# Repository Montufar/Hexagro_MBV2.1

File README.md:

# Hexagro_MBV2.1
Schematic, BOM and PCB layout of V2.1 Motherboard

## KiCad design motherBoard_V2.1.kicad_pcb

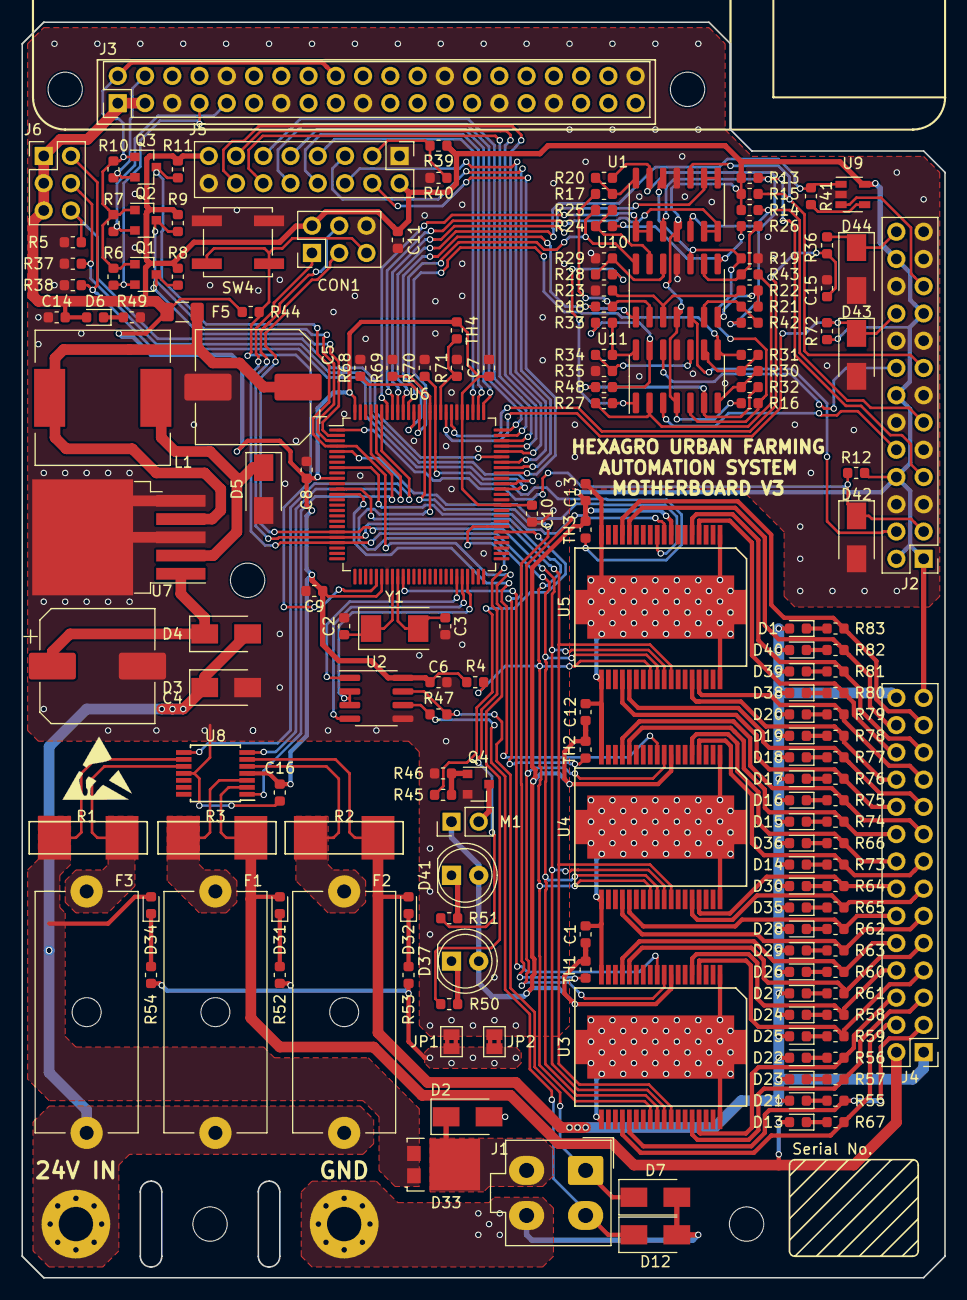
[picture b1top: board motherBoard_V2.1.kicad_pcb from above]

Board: 2 copper layers, 86.0 x 117.0 mm, 175 parts (0 on the bottom side), 155 nets.

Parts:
C1, C12, C13: 1uF; C_0603_1608Metric
C2, C3: 18pF; C_0603_1608Metric
C4: 680uF; CP_Elec_10x10.5
C5: 220uF; CP_Elec_10x10.5
C6, C7, C8, C9, C10, C11, C14, C15: 100nF; C_0603_1608Metric
C16: 100 nF; C_0603_1608Metric
CON1: AVR-ISP-6; PinHeader_2x03_P2.54mm_Vertical
D1, D6, D13, D14, D15, D16, D17, D18, D19, D20, D21, D22, D23, D24, D25, D26, D27, D28, D29, D30, D31, D32, D34, D35, D36, D38, D39, D40: LED; LED_0603_1608Metric
D2: D_TVS_24V; D_SMA
D3, D4, D5: D; D_SMA
D7, D12, D42, D43, D44: D_TVS_5V; D_SMA
D33: STPS1045SF; TO-277A
D37, D41: LED_ALT; LED_D5.0mm
F1, F2: 1 A; Fuseholder_Cylinder-5x20mm_Schurter_0031_8201_Horizontal_Op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
F3: 7.5 A; Fuseholder_Cylinder-5x20mm_Schurter_0031_8201_Horizontal_Op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
F5: 1A; Fuse_1206_3216Metric
J1: Conn_LEDs; Molex_Mini-Fit_Jr_5566-04A_2x02_P4.20mm_Vertical
J2: Conn_02x13_Odd_Even; PinHeader_2x13_P2.54mm_Vertical
J3: Conn_RPi3; PinHeader_2x20_P2.54mm_Vertical
J4: Conn_02x14_Odd_Even; PinHeader_2x14_P2.54mm_Vertical
J5: Conn_02x08_Odd_Even; PinHeader_2x08_P2.54mm_Vertical
J6: Conn_02x03_Odd_Even; PinHeader_2x03_P2.54mm_Vertical
JP1, JP2: SolderJumper_2_Bridged; SolderJumper-2_P1.3mm_Bridged2Bar_Pad1.0x1.5mm
L1: 33uH; L_12x12mm_H8mm
M1: Fan; PinHeader_1x02_P2.54mm_Vertical
Q1, Q2, Q3: BSS138; SOT-23
Q4: 2N7002; SOT-23
R1: 10m; OARS1
R2, R3: 50m; OARS1
R4, R5, R6, R7, R8, R9, R10, R11, R12, R13, R14, R15, R37, R38, R40, R41, R44, R46, R68, R69, R70, R71: 10k; R_0603_1608Metric
R16, R19, R49, R50, R51: 1k; R_0603_1608Metric
R17, R18, R22, R23, R24, R25, R28, R29, R30, R31, R34, R35: 40k; R_0603_1608Metric
R20, R21, R26, R27, R32, R33: 25k; R_0603_1608Metric
R36, R42, R43, R45, R47, R48: 100; R_0603_1608Metric
R39: 27k; R_0603_1608Metric
R52, R53, R54, R55, R56, R57, R58, R59, R60, R61, R62, R63, R64, R65, R66, R67, R72, R73, R74, R75, R76, R77, R78, R79, R80, R81, R82, R83: 22k; R_0603_1608Metric
SW4: SW_Push; SW_Push_1P1T_NO_CK_KSC6xxJ
TH1, TH2, TH3, TH4: Thermistor_NTC; R_0603_1608Metric
U1, U10, U11: MCP6004; SOIC-14_3.9x8.7mm_P1.27mm
U2: MAX485E; SOIC-8_3.9x4.9mm_P1.27mm
U3, U4, U5: TLE6230GP; PG-DSO-36
U6: ATMEGA2560-16AU; TQFP-100_14x14mm_P0.5mm
U7: LM2596S-5; TO-263-5_TabPin3
U8: INA4180A2IPWR; TSSOP-14_4.4x5mm_P0.65mm
U9: MCP6001; SOT-23-5
Y1: 16 MHz; Crystal_SMD_0603-2Pin_6.0x3.5mm

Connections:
+5V: C1.1, C6.1, C7.1, C8.1, C9.1, C10.1, C11.1, C12.1, C13.1, C14.1, C16.1, CON1.2, D6.2, D37.2, D41.2, F5.1, J2.1, J2.2, J2.8, J2.14, J2.19, J2.24, J3.1, J3.3, J4.27, J5.2, J5.15, J6.1, J6.3, J6.5, M1.1, R4.1, R8.1, R9.1, R11.1, R12.2, R13.1, R14.1, R15.1, R16.1, R39.1, R44.1, R72.1, TH1.1, TH2.1, TH3.1, TH4.1, U1.4, U2.8, U3.8, U4.8, U5.8, U6.10, U6.31, U6.61, U6.80, U6.100, U8.4, U9.5, U10.4, U11.4
+24V_IN: D3.1, D4.2, F1.2, F2.2, F3.2
+24V_LEDS: D33.1, D33.2, D34.2, R1.1, U8.9
+24V_PUMP: D13.2, D31.2, J4.2, R3.1, U8.2
+24V_VALVES: D1.2, D14.2, D15.2, D16.2, D17.2, D18.2, D19.2, D20.2, D21.2, D22.2, D23.2, D24.2, D25.2, D26.2, D27.2, D28.2, D29.2, D30.2, D32.2, D35.2, D36.2, D38.2, D39.2, D40.2, J4.1, J4.28, R2.1, U8.6
/CO2_SIG: D44.1, J2.26, R36.2
/DHT_SIG: D42.1, J2.3, R12.1, U6.1
/IN+1: F1.1, R3.2, U8.3
/IN+2: F2.1, R2.2, U8.5
/IN+3: F3.1, R1.2, U8.10
/LC_1: J2.4, U10.5
/LC_2: J2.10, U11.3
/LC_3: J2.16, U11.12
/LS_SIG: D43.1, J2.20, R72.2, U6.83
/MCU/ADC0: U6.97, U8.1
/MCU/ADC1: U6.96, U8.7
/MCU/ADC2: U6.95, U8.8
/MCU/ADC3: U1.1, U1.2, U6.94
/MCU/ADC4: U1.6, U1.7, U6.93
/MCU/ADC5: U1.8, U1.9, U6.92
/MCU/ADC6: R41.1, U6.91, U9.1
/MCU/ADC7: R18.1, U6.90, U10.1
/MCU/ADC8: R25.1, U6.89, U10.14
/MCU/ADC9: R31.1, U6.88, U11.8
/MCU/ADC10: R68.1, TH1.2, U6.87
/MCU/ADC11: R69.1, TH2.2, U6.86
/MCU/ADC12: R70.1, TH3.2, U6.85
/MCU/ADC13: R71.1, TH4.2, U6.84
/MCU/ADC15: C15.1, R36.1, U6.82
/MCU/DRV_FLT: R4.2, U3.26, U4.26, U5.26, U6.12
/MCU/DRV_RESET: U3.9, U4.9, U5.9, U6.8
/MCU/MCU_RESET: CON1.5, R44.2, SW4.2, U6.30
/MCU/MISO: CON1.1, U3.27, U4.27, U5.27, U6.22
/MCU/MOSI: CON1.4, U3.29, U4.29, U5.29, U6.21
/MCU/RX0_MCU: Q1.3, R8.2, U6.2
/MCU/SCK: CON1.3, U3.28, U4.28, U5.28, U6.20
/MCU/ctrl_mod: J6.6, R5.1, U6.70
/MCU/ctrl_run: J6.2, R38.1, U6.64
/MCU/ctrl_sel: J6.4, R37.1, U6.65
/MCU/disp_db0: J5.7, U6.78
/MCU/disp_db1: J5.8, U6.77
/MCU/disp_db2: J5.9, U6.76
/MCU/disp_db3: J5.10, U6.75
/MCU/disp_db4: J5.11, U6.74
/MCU/disp_db5: J5.12, U6.73
/MCU/disp_db6: J5.13, U6.72
/MCU/disp_db7: J5.14, U6.71
/MCU/disp_e: J5.6, U6.69
/MCU/disp_rs: J5.4, U6.67
/MCU/disp_rw: J5.5, U6.68
/NTC_W1: J2.7, R13.2, U1.3
/NTC_W2: J2.11, R14.2, U1.5
/NTC_W3: J2.15, R15.2, U1.10
/RS485/DE: U2.2, U2.3, U6.47
/RS485/DI: U2.4, U6.46
/RS485/RO: U2.1, U6.45
/RaspberryPi3Conn/3V3_RPI: J3.2, J3.18, Q1.1, Q2.1, Q3.1, R6.1, R7.1, R10.1
/RaspberryPi3Conn/GPIO2_RPI: J3.4, Q3.2, R10.2
/RaspberryPi3Conn/RX_RPI: Q2.3, R9.2, U6.3
/RaspberryPi3Conn/UART0_RX_RPI: J3.9, Q2.2, R7.2
/RaspberryPi3Conn/UART0_TX_RPI: J3.7, Q1.2, R6.2
/WPS_SIG: J2.21, U9.3
/fanDriver/DRIVE: R45.2, U6.56
/lowSideDriver1/CS: U3.10, U6.35
/lowSideDriver2/CS: U4.10, U6.13
/lowSideDriver3/CS: U5.10, U6.5
GND: C2.2, C3.2, C4.2, C5.2, C6.2, C7.2, C8.2, C9.2, C10.2, C11.2, C14.2, C15.2, C16.2, CON1.6, D3.2, D5.2, D42.2, D43.2, D44.2, J2.5, J2.6, J2.9, J2.12, J2.13, J2.17, J2.18, J2.22, J2.23, J2.25, J3.5, J3.10, J3.13, J3.19, J3.26, J3.29, J3.33, J3.40, J5.1, J5.16, JP1.2, JP2.2, Q4.2, R5.2, R19.2, R23.1, R29.1, R35.1, R37.2, R38.2, R40.2, R46.1, R49.1, R68.2, R69.2, R70.2, R71.2, SW4.1, U1.11, U2.5, U6.11, U6.32, U6.62, U6.81, U6.99, U7.3, U7.5, U8.11, U9.2, U10.11, U11.11
GNDPWR: C1.2, C12.2, C13.2, D2.2, D7.2, D12.2, J1.4, JP1.1, JP2.1, R52.1, R53.1, R54.1, U3.1, U3.18, U3.19, U3.36, U3.37, U4.1, U4.18, U4.19, U4.36, U4.37, U5.1, U5.18, U5.19, U5.36, U5.37
IO0: Q3.3, R11.2, R50.1, U6.4
MCU_DEBUG: R51.1, U6.57
MISC_LOW_SIDE_1: J4.15, R73.1, U4.4
MISC_LOW_SIDE_2: J4.18, R74.1, U4.14
MISC_LOW_SIDE_3: J4.17, R75.1, U4.15
MISC_LOW_SIDE_4: J4.20, R76.1, U5.22
MISC_LOW_SIDE_5: J4.19, R77.1, U5.23
MISC_LOW_SIDE_6: J4.22, R78.1, U5.32
MISC_LOW_SIDE_7: J4.21, R79.1, U5.33
MISC_LOW_SIDE_8: J4.24, R80.1, U5.4
MISC_LOW_SIDE_9: J4.23, R81.1, U5.5
MISC_LOW_SIDE_10: J4.26, R82.1, U5.14
MISC_LOW_SIDE_11: J4.25, R83.1, U5.15
unnamed: C2.1, U6.33, Y1.1
unnamed: C3.1, U6.34, Y1.2
unnamed: C4.1, D4.1, U7.1
unnamed: C5.1, F5.2, L1.2, U7.4
unnamed: D1.1, R83.2
unnamed: D2.1, D33.3, J1.3
unnamed: D5.1, L1.1, U7.2
unnamed: D6.1, R49.2
unnamed: D13.1, R67.2
unnamed: D14.1, R73.2
unnamed: D15.1, R74.2
unnamed: D16.1, R75.2
unnamed: D17.1, R76.2
unnamed: D18.1, R77.2
unnamed: D19.1, R78.2
unnamed: D20.1, R79.2
unnamed: D21.1, R55.2
unnamed: D22.1, R56.2
unnamed: D23.1, R57.2
unnamed: D24.1, R58.2
unnamed: D25.1, R59.2
unnamed: D26.1, R60.2
unnamed: D27.1, R61.2
unnamed: D28.1, R62.2
unnamed: D29.1, R63.2
unnamed: D30.1, R64.2
unnamed: D31.1, R52.2
unnamed: D32.1, R53.2
unnamed: D34.1, R54.2
unnamed: D35.1, R65.2
unnamed: D36.1, R66.2
unnamed: D37.1, R50.2
unnamed: D38.1, R80.2
unnamed: D39.1, R81.2
unnamed: D40.1, R82.2
unnamed: D41.1, R51.2
unnamed: J5.3, R39.2, R40.1
unnamed: M1.2, Q4.3
unnamed: Q4.1, R45.1, R46.2
unnamed: R16.2, R19.1, U1.12, U10.10, U11.5
unnamed: R17.1, R18.2, U10.2
unnamed: R17.2, R20.1, U1.14
unnamed: R20.2, R42.1, U1.13
unnamed: R21.1, R42.2, U10.6
unnamed: R21.2, R22.2, U10.7
unnamed: R22.1, R23.2, U10.3
unnamed: R24.1, R25.2, U10.13
unnamed: R24.2, R26.1, U10.8
unnamed: R26.2, R43.1, U10.9
unnamed: R27.1, R43.2, U11.2
unnamed: R27.2, R28.2, U11.1
unnamed: R28.1, R29.2, U10.12
unnamed: R30.1, R31.2, U11.9
unnamed: R30.2, R32.1, U11.7
unnamed: R32.2, R48.1, U11.6
unnamed: R33.1, R48.2, U11.13
unnamed: R33.2, R34.2, U11.14
unnamed: R34.1, R35.2, U11.10
unnamed: R41.2, U9.4
PUMP_LOW_SIDE: J4.4, R67.1, U3.22
RS_485-A: D12.1, J1.2, R47.2, U2.6
RS_485-B: D7.1, J1.1, R47.1, U2.7
VALVE_1_LOW_SIDE: J4.3, R55.1, U3.23
VALVE_2_LOW_SIDE: J4.6, R56.1, U3.33
VALVE_3_LOW_SIDE: J4.5, R57.1, U3.32
VALVE_4_LOW_SIDE: J4.8, R58.1, U3.5
VALVE_5_LOW_SIDE: J4.7, R59.1, U3.4
VALVE_6_LOW_SIDE: J4.10, R60.1, U3.15
VALVE_7_LOW_SIDE: J4.9, R61.1, U3.14
VALVE_8_LOW_SIDE: J4.12, R62.1, U4.23
VALVE_9_LOW_SIDE: J4.11, R63.1, U4.22
VALVE_10_LOW_SIDE: J4.14, R64.1, U4.33
VALVE_11_LOW_SIDE: J4.13, R65.1, U4.32
VALVE_12_LOW_SIDE: J4.16, R66.1, U4.5

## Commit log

2020-04-22 Create MCU
